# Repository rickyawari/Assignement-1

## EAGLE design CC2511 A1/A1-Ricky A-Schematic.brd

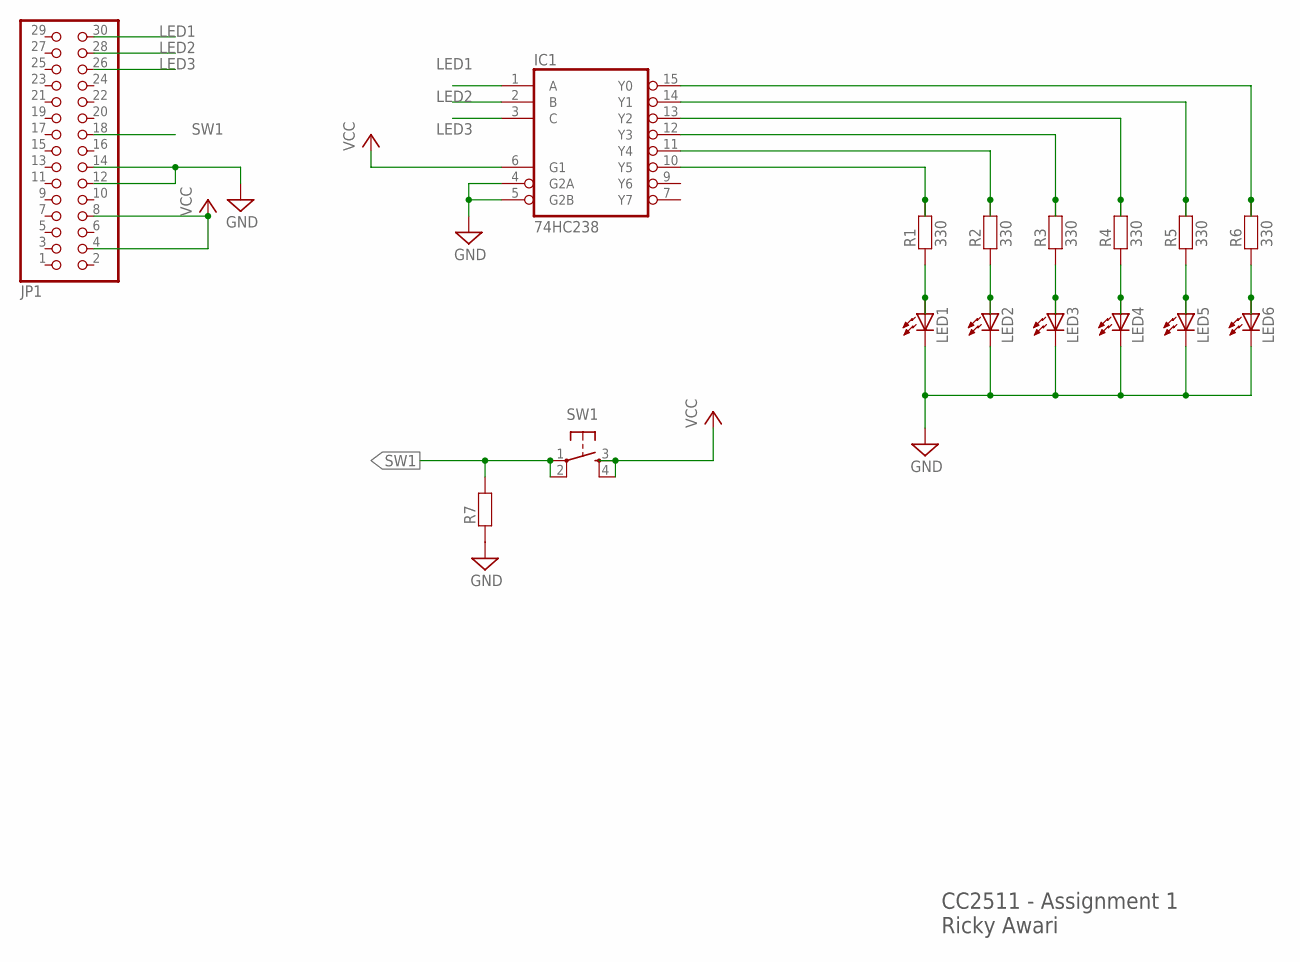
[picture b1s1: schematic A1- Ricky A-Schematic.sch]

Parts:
IC1: 74HC238; DIL16
JP1: PINHD-2X15; 2X15
LED1, LED2, LED3, LED4, LED5, LED6: LED-5MM
R1, R2, R3, R4, R5, R6: 330; AXIAL-0.4
R7: RESISTOR-AXIAL-0.4; AXIAL-0.4
SW1: TAC_SWITCHPTH; TACTILE-PTH

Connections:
GND: IC1.4 (G2A), IC1.5 (G2B), IC1.8 (GND), JP1.12, JP1.14, LED1.C, LED2.C, LED3.C, LED4.C, LED5.C, LED6.C, R7.P$1 (1)
LED1: IC1.1 (A), JP1.30
LED2: IC1.2 (B), JP1.28
LED3: IC1.3 (C), JP1.26
unnamed: IC1.10 (Y5), R1.P$2 (2)
unnamed: IC1.11 (Y4), R2.P$2 (2)
unnamed: IC1.12 (Y3), R3.P$2 (2)
unnamed: IC1.13 (Y2), R4.P$2 (2)
unnamed: IC1.14 (Y1), R5.P$2 (2)
unnamed: IC1.15 (Y0), R6.P$2 (2)
unnamed: LED1.A, R1.P$1 (1)
unnamed: LED2.A, R2.P$1 (1)
unnamed: LED3.A, R3.P$1 (1)
unnamed: LED4.A, R4.P$1 (1)
unnamed: LED5.A, R5.P$1 (1)
unnamed: LED6.A, R6.P$1 (1)
SW1: JP1.18, R7.P$2 (2), SW1.1, SW1.2
VCC: IC1.6 (G1), IC1.16 (VCC), JP1.4, JP1.8, SW1.3, SW1.4

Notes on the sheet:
CC2511 - Assignment 1 Ricky Awari

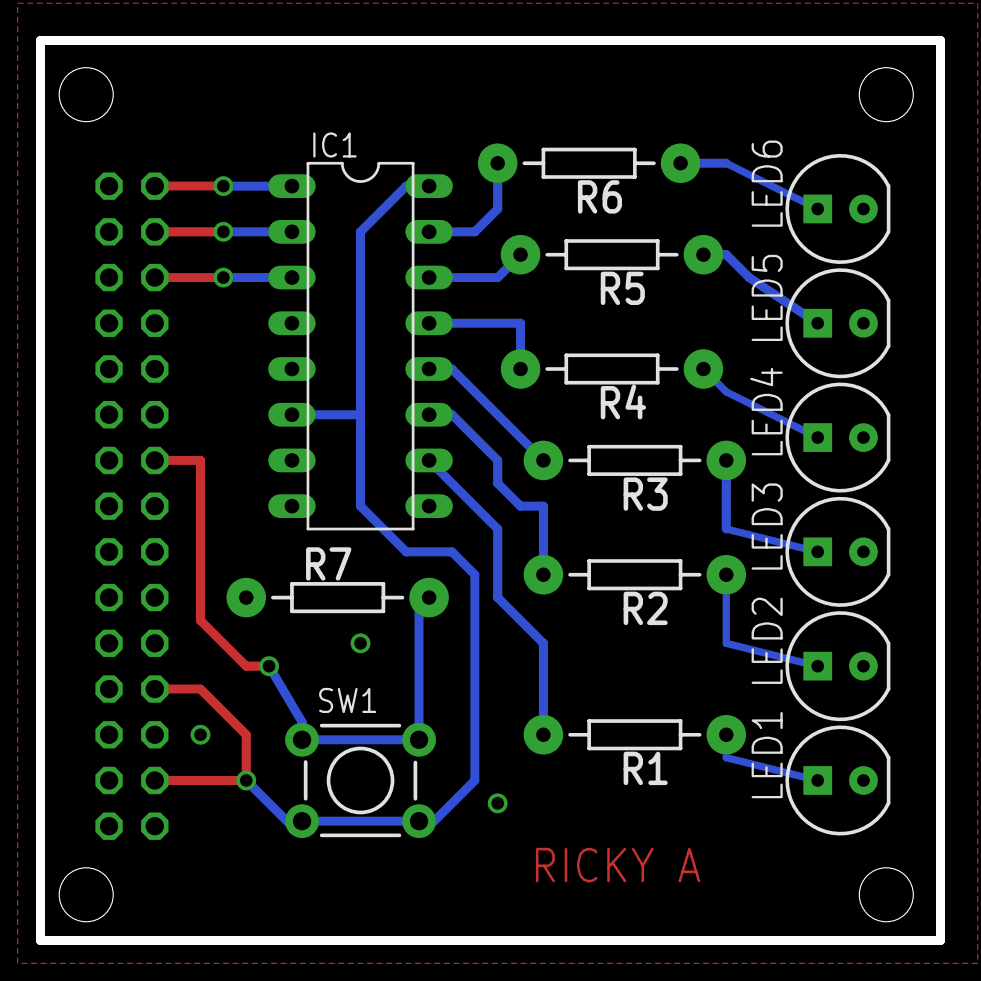
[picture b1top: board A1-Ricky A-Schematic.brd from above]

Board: 2 copper layers, 50.0 x 50.0 mm, 16 parts (1 on the bottom side), 18 nets.

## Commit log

2014-09-05 :space_invader: Added .gitattributes & .gitignore files
2014-09-05 Assignement1

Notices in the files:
parts and their libraries:
SparkFun-Electromechanical: Licensing: Creative Commons ShareAlike 4.0 International - https://creativecommons.org/licenses/by-sa/4.0
